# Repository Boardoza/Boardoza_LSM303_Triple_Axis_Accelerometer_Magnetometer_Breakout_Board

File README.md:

# Boardoza LSM303 Triple Axis Accelerometer & Magnetometer Breakout Board

The **Boardoza LSM303 Breakout Board** is a compact and ultra-low-power motion sensing solution featuring the **STMicroelectronics LSM303AGR** 6-axis e-compass sensor. It combines a **3-axis digital accelerometer** and a **3-axis digital magnetometer** in a single package, enabling accurate motion tracking, orientation sensing, and tilt-compensated compass applications.

Designed for seamless integration with both modern and legacy development platforms, the board includes a **TXS0104 bi-directional logic level shifter**, allowing direct compatibility with both **3.3V and 5V microcontrollers** such as ESP32, STM32, Raspberry Pi Pico, and Arduino Uno. With support for high-speed I<sup>2</sup>C communication and advanced interrupt functionality, this board is ideal for **robotics, wearable devices, navigation systems, drones, IoT applications, and smart motion-based projects**.

| Front Side | Back Side |
|:---:|:---:|
|  |  |

---

## Key Features

- **Integrated 6-Axis Motion Sensor:** Combines a 3-axis accelerometer and 3-axis magnetometer in a single compact module.
- **True E-Compass Functionality:** Enables accurate heading and orientation measurements using tilt compensation.
- **Wide Logic Compatibility:** Built-in TXS0104 level shifter supports both 3.3V and 5V systems.
- **High-Speed I<sup>2</sup>C Communication:** Supports Standard, Fast Mode (400kHz), and Fast Mode Plus (1MHz).
- **Ultra-Low Power Operation:** Optimized for battery-powered and energy-efficient embedded systems.
- **Programmable Interrupts:** Supports free-fall detection, orientation sensing, magnetic threshold detection, and motion events.

---

## Technical Specifications

**Model:** LSM303AGRTR  
**Manufacturer:** Boardoza    
**Manufacturer IC:** STMicroelectronics   
**Sensor Type:** 3-Axis Accelerometer + 3-Axis Magnetometer  
**Input Voltage:** 3.3 VDC - 5V DC  
**Voltage Logic Compatibility:** 3.3V / 5V (via TXS0104 Level Shifter)  
**Communication Interface:** I<sup>2</sup>C  / SPI  
**I<sup>2</sup>C Speed:** Standard Mode (100kHz), Fast Mode (400kHz), Fast Mode Plus (1MHz)   
**Accelerometer Full Scale Range:** ±2g / ±4g / ±8g / ±16g  
**Magnetic Field Range:** ±50 gauss  
**Accelerometer Resolution:** 12-bit  
**Magnetometer Resolution:** 16-bit  
**Functions:** Motion Detection, Orientation Sensing, Digital Compass, Tilt Compensation  
**Interrupt Features:** Free-fall, 6D/4D orientation, magnetic threshold interrupt  
**Operating Temperature:** -40°C to +85°C  
**Board Dimensions:** 20mm x 20mm  

---

## Board Pinout

### ( J1 ) Main Communication Connector

| Pin Number | Pin Name | Description |
|:---:|:---:|---|
| 1 | VCC | Voltage Supply Input |
| 2 | SDA / SDI / SDO | I<sup>2</sup>C Data / SPI Data Input / 3-wire SPI Data Output |
| 3 | /CS_MAG | Active-Low Magnetometer SPI Chip Select |
| 4 | /CS_XL | Active-Low Accelerometer SPI Chip Select |
| 5 | SCL / SPC | I<sup>2</sup>C Clock / SPI Clock |
| 6 | GND | Ground |

### ( J2 ) Interrupt Connector

| Pin Number | Pin Name | Description |
|:---:|:---:|---|
| 1 | XL1 | Accelerometer Interrupt Output 1 (3.3V Logic) |
| 2 | XL2 | Accelerometer Interrupt Output 2 (3.3V Logic) |
| 3 | MAG | Magnetometer Interrupt / Data Ready Output (3.3V Logic) |

---

## Board Dimensions

---

## Step Files

[Boardoza LSM303AGRTR.step](./assets/LSM303%20Step.step)

---

## Datasheet

[LSM303AGR Datasheet.pdf](./assets/LSM303%20Datasheet.pdf)

---

## Version History

- V1.0.0 - Initial Release

---

## Support

- If you have any questions or need support, please contact support@boardoza.com

---

## **License**

This repository contains both hardware and software components:

### **Hardware Design**

[![CC BY-SA 4.0][cc-by-sa-shield]][cc-by-sa]

All hardware design files are licensed under [Creative Commons Attribution-ShareAlike 4.0 International License][cc-by-sa].

[cc-by-sa]: http://creativecommons.org/licenses/by-sa/4.0/
[cc-by-sa-shield]: https://img.shields.io/badge/License-CC%20BY--SA%204.0-lightgrey.svg

### **Software/Firmware**

[![BSD-3-Clause][bsd-shield]][bsd]

All software and firmware are licensed under [BSD 3-Clause License][bsd].

[bsd]: https://opensource.org/licenses/BSD-3-Clause
[bsd-shield]: https://img.shields.io/badge/License-BSD%203--Clause-blue.svg

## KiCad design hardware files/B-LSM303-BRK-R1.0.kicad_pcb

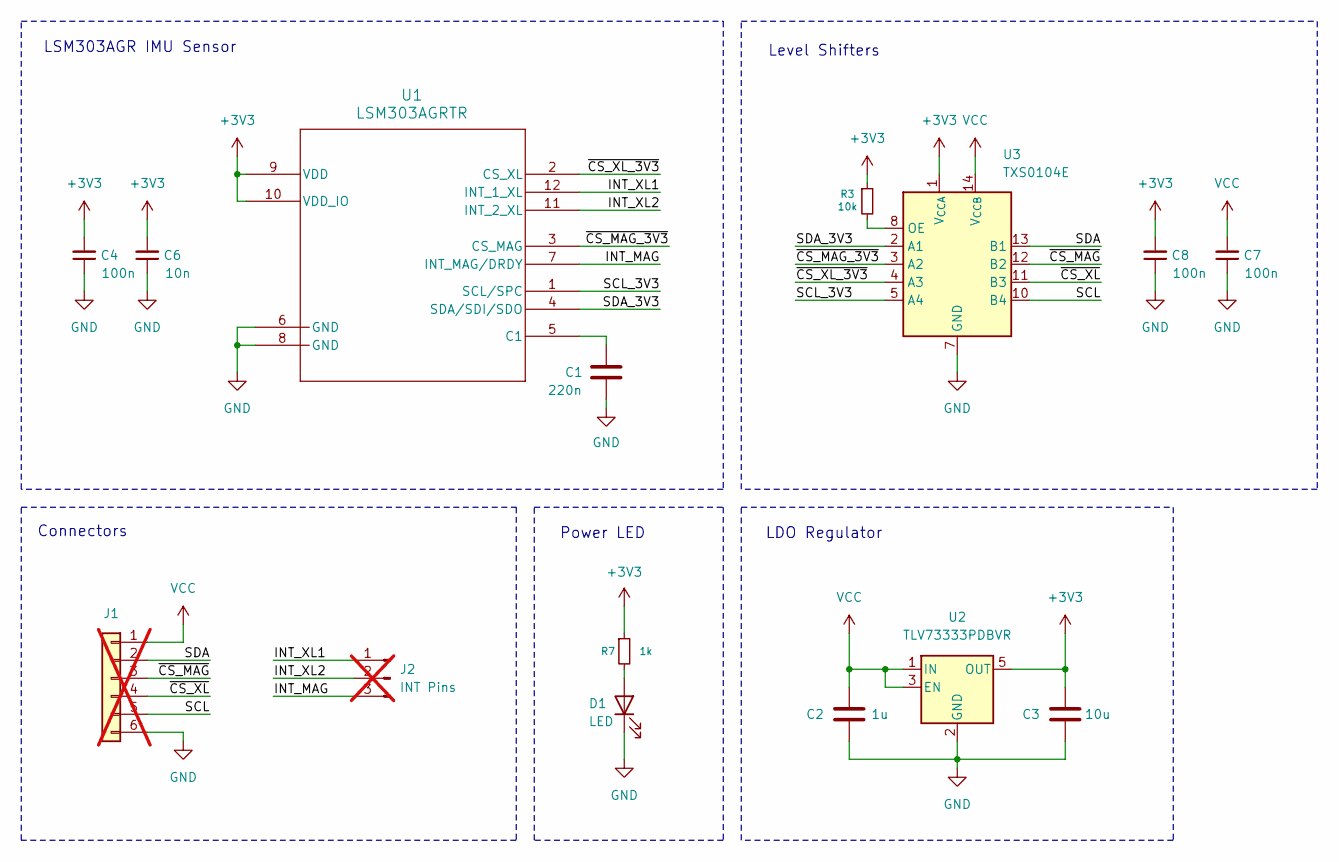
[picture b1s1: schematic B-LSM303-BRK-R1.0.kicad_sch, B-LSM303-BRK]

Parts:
C1: 220n; C_0402_1005Metric; MPN MCF02KTX100224
C2: 1u; C_0402_1005Metric; MPN CL05A105KO5NNNC
C3: 10u; C_0402_1005Metric; MPN CL05A106MP5NUNC
C4, C7, C8: 100n; C_0402_1005Metric; MPN CL05B104KO5NNNC
C6: 10n; C_0402_1005Metric; MPN CL05B103KA5NNNC
D1: LED; LED_0402_1005Metric; MPN 16-213SURC/S530-A3/TR8
J1: Conn_01x06; JST_XH_B6B-XH-A_1x06_P2.50mm_Vertical; MPN L-KLS1-2.50-06-SB; not fitted
J2: INT Pins; PinHeader_1x03_P2.54mm_Vertical; MPN L-KLS1-207-1-03-S; not fitted
R3: 10k; R_0402_1005Metric; MPN CRT02J6E1002
R7: 1k; R_0402_1005Metric; MPN 0402WGJ0102TCE
U1: LSM303AGRTR; SON_03AGRTR_STM; MPN LSM303AGRTR
U2: TLV73333PDBVR; SOT-23-5; MPN TLV73333PDBVR
U3: TXS0104E; Texas_S-PVQFN-N14; MPN TXS0104ERGYR

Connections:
+3V3: C3.1, C4.2, C6.2, C8.2, R3.1, R7.1, U1.9 (VDD), U1.10 (VDD_IO), U2.5 (OUT), U3.1 (V_{CCA})
/INT_MAG: J2.3, U1.7 (INT_MAG/DRDY)
/INT_XL1: J2.1, U1.12 (INT_1_XL)
/INT_XL2: J2.2, U1.11 (INT_2_XL)
/SCL: J1.5, U3.10 (B4)
/SCL_3V3: U1.1 (SCL/SPC), U3.5 (A4)
/SDA: J1.2, U3.13 (B1)
/SDA_3V3: U1.4 (SDA/SDI/SDO), U3.2 (A1)
/~CS_MAG_3V3: U1.3 (CS_MAG), U3.3 (A2)
/~CS_MAG: J1.3, U3.12 (B2)
/~CS_XL_3V3: U1.2 (CS_XL), U3.4 (A3)
/~CS_XL: J1.4, U3.11 (B3)
GND: C1.1, C2.1, C3.2, C4.1, C6.1, C7.1, C8.1, D1.1 (K), J1.6, U1.6 (GND), U1.8 (GND), U2.2 (GND), U3.7 (GND), U3.15
unnamed: D1.2 (A), R7.2
unnamed: C1.2, U1.5 (C1)
unnamed: R3.2, U3.8 (OE)
VCC: C2.2, C7.2, J1.1, U2.1 (IN), U2.3 (EN), U3.14 (V_{CCB})

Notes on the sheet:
Connectors
LDO Regulator
Power LED
LSM303AGR IMU Sensor
Level Shifters

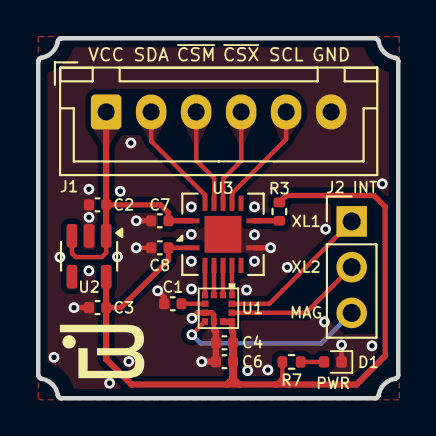
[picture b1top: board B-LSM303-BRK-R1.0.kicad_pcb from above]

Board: 2 copper layers, 20.0 x 20.0 mm, 15 parts (0 on the bottom side), 17 nets.
